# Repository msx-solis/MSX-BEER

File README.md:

# MSX-BEER
The MSX-Beer202 is a simple IDE interface for the MSX computers that not require to have more than 64K to use a hard disk. Original design by Solid and improved by some others (Yeti, FabF,...) in their own versions.

MSXmakers version 1.1 on "beer_ide_kicad" and "gerber" folders.

More info:

Links for ide-beer202:

Here you have very good instructions (in portuguesse). Talk about the problems with some 82c55 versions and how to format with "SD fortater".
(Full overWrite y size adjustament = on).

http://basshp.blogspot.com/2014/04/beer-202-ata-ide-review.html

Here you have a demostration video for this distribution: https://www.youtube.com/watch?v=AeNEiQcKNEI&t=1s

And here you have lots of BEER interface details

https://www.pjrc.com/tech/8051/ide/wesley.html

Some more links

https://www.msx.org/wiki/Beer_202

https://hansotten.file-hunter.com/do-it-yourself/beer-ide/

https://www.pjrc.com/tech/8051/ide/wesley.html

https://www.msx.org/es/news/software/es/beer-202-ide-interface-utilidad-de-particionado

https://www.msx.org/forum/msx-talk/hardware/beer-202-ide-interface?page=2

http://www.retrocomputacion.com/forum/hardware_msx/4440/experimentos-con-la-beer-interface-ide-para-msx-1-y-2/&p=2

Some files:

https://msx.org/forum/msx-talk/hardware/beer-ide-bios-19rc1-source-code-wanted?page=1

https://sysadminmosaic.ru/en/msx/beer_ide/beer_ide

Discussion about the version SD and some more files:

http://www.nedopc.org/forum/viewtopic.php?f=96&t=18820&sid=d75385e94fd1d6dbab35a1f73d379176&start=45#p144050

Another software to clone RAW disks called HDD Raw Copy Rool v1.10 (for windows):

http://www.hddguru.com/

Another system menu for game loading.

https://www.msxall.com/download/msxmenu-v1.68-beer.zip

And here you have a demostration video for this ditribution: https://www.youtube.com/watch?v=a2agPfgZmI0&t=596s

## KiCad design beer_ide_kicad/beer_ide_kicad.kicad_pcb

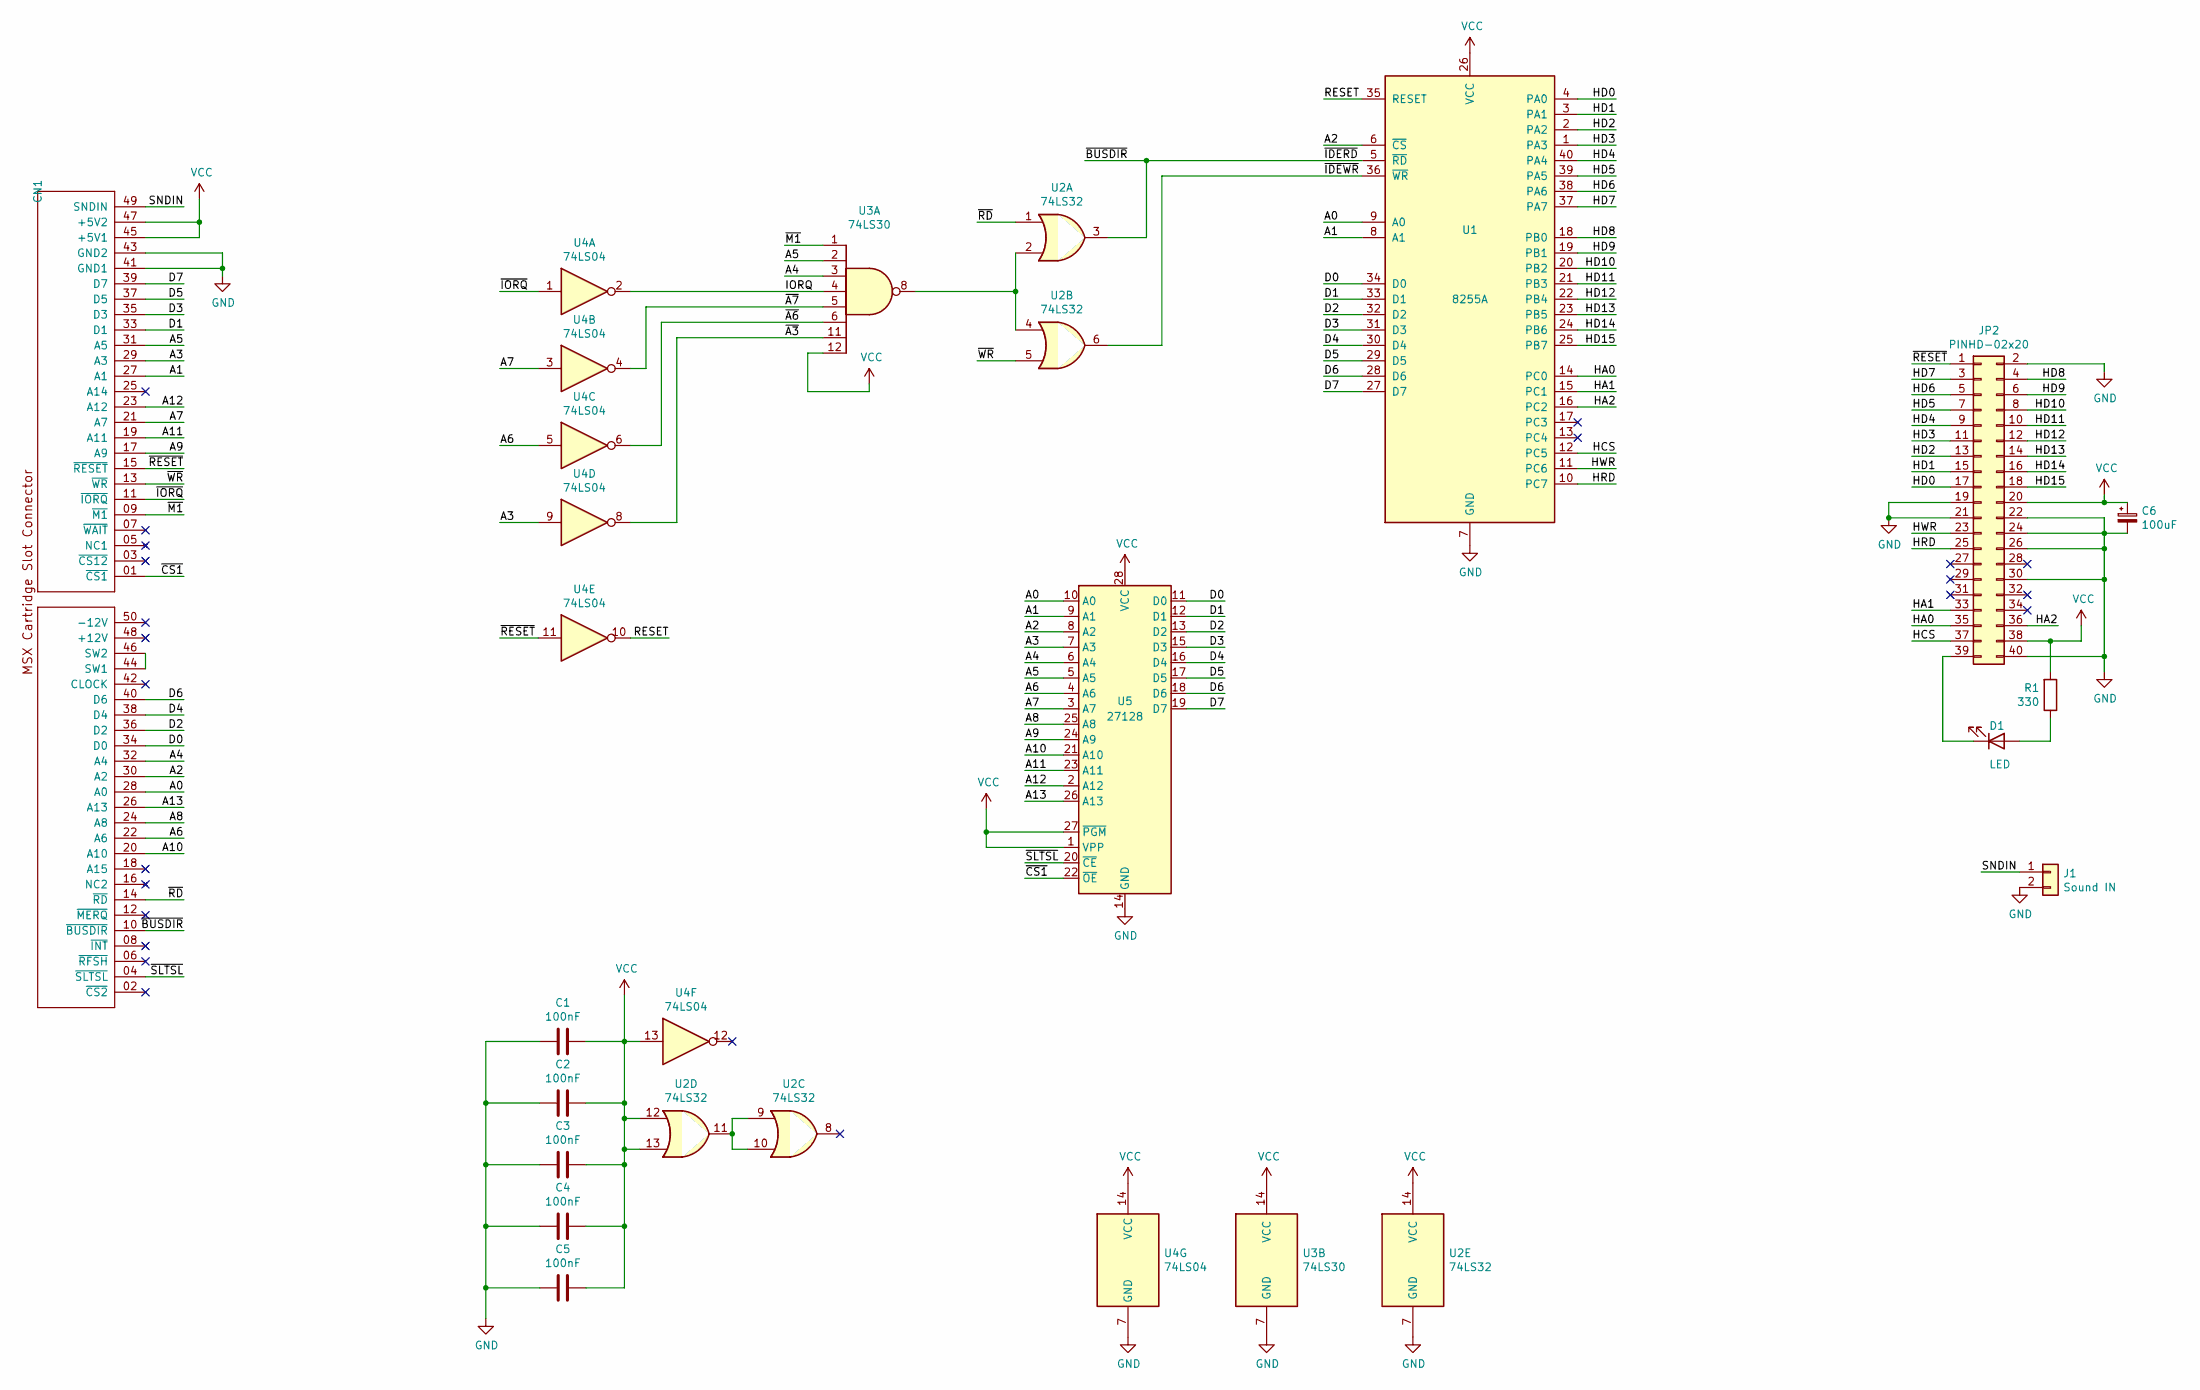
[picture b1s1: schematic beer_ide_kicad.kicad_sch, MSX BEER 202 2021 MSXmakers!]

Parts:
C1, C2, C3, C4, C5: 100nF; C_Disc_D4.7mm_W2.5mm_P5.00mm
C6: 100uF; CP_tumbado
CN1: MSX_SLOT_CON; CARTRIDGE_#_MSX_XL
D1: LED; LED_D3.0mm
J1: Sound IN; JST_EH_S2B-EH_1x02_P2.50mm_Horizontal
JP2: PINHD-02x20; PinHeader_2x20_P2.54mm_Horizontal
R1: 330; R_Axial_DIN0207_L6.3mm_D2.5mm_P7.62mm_Horizontal
U1: 8255A; DIP-40c_W15.24mm_LongPads
U2: 74LS32; DIP-14_W7.62mm_LongPads_0.9
U3: 74LS30; DIP-14c_W7.62mm_LongPads
U4: 74LS04; DIP-14c_W7.62mm_LongPads
U5: 27128; DIP-28c_W15.24mm_Socket_LongPads

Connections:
/A0: CN1.28 (A0), U1.9 (A0), U5.10 (A0)
/A1: CN1.27 (A1), U1.8 (A1), U5.9 (A1)
/A2: CN1.30 (A2), U1.6 (~CS), U5.8 (A2)
/A3: CN1.29 (A3), U4.9, U5.7 (A3)
/A4: CN1.32 (A4), U3.3, U5.6 (A4)
/A5: CN1.31 (A5), U3.2, U5.5 (A5)
/A6: CN1.22 (A6), U4.5, U5.4 (A6)
/A7: CN1.21 (A7), U4.3, U5.3 (A7)
/A8: CN1.24 (A8), U5.25 (A8)
/A9: CN1.17 (A9), U5.24 (A9)
/A10: CN1.20 (A10), U5.21 (A10)
/A11: CN1.19 (A11), U5.23 (A11)
/A12: CN1.23 (A12), U5.2 (A12)
/A13: CN1.26 (A13), U5.26 (A13)
/D0: CN1.34 (D0), U1.34 (D0), U5.11 (D0)
/D1: CN1.33 (D1), U1.33 (D1), U5.12 (D1)
/D2: CN1.36 (D2), U1.32 (D2), U5.13 (D2)
/D3: CN1.35 (D3), U1.31 (D3), U5.15 (D3)
/D4: CN1.38 (D4), U1.30 (D4), U5.16 (D4)
/D5: CN1.37 (D5), U1.29 (D5), U5.17 (D5)
/D6: CN1.40 (D6), U1.28 (D6), U5.18 (D6)
/D7: CN1.39 (D7), U1.27 (D7), U5.19 (D7)
/HA0: JP2.35, U1.14 (PC0)
/HA1: JP2.33, U1.15 (PC1)
/HA2: JP2.36, U1.16 (PC2)
/HCS: JP2.37, U1.12 (PC5)
/HD0: JP2.17, U1.4 (PA0)
/HD1: JP2.15, U1.3 (PA1)
/HD2: JP2.13, U1.2 (PA2)
/HD3: JP2.11, U1.1 (PA3)
/HD4: JP2.9, U1.40 (PA4)
/HD5: JP2.7, U1.39 (PA5)
/HD6: JP2.5, U1.38 (PA6)
/HD7: JP2.3, U1.37 (PA7)
/HD8: JP2.4, U1.18 (PB0)
/HD9: JP2.6, U1.19 (PB1)
/HD10: JP2.8, U1.20 (PB2)
/HD11: JP2.10, U1.21 (PB3)
/HD12: JP2.12, U1.22 (PB4)
/HD13: JP2.14, U1.23 (PB5)
/HD14: JP2.16, U1.24 (PB6)
/HD15: JP2.18, U1.25 (PB7)
/HRD: JP2.25, U1.10 (PC7)
/HWR: JP2.23, U1.11 (PC6)
/IORQ: U3.4, U4.2
/RESET: U1.35 (RESET), U4.10
/SNDIN: CN1.49 (SNDIN), J1.1
/~A3: U3.11, U4.8
/~A6: U3.6, U4.6
/~A7: U3.5, U4.4
/~BUSDIR: CN1.10 (~BUSDIR), U1.5 (~RD), U2.3
/~CS1: CN1.01 (~CS1), U5.22 (~OE)
/~IDEWR: U1.36 (~WR), U2.6
/~IORQ: CN1.11 (~IORQ), U4.1
/~M1: CN1.09 (~M1), U3.1
/~RD: CN1.14 (~RD), U2.1
/~RESET: CN1.15 (~RESET), JP2.1, U4.11
/~SLTSL: CN1.04 (~SLTSL), U5.20 (~CE)
/~WR: CN1.13 (~WR), U2.5
GND: C1.2, C2.2, C3.2, C4.2, C5.2, C6.2, CN1.41 (GND1), CN1.43 (GND2), J1.2, JP2.2, JP2.19, JP2.21, JP2.22, JP2.24, JP2.26, JP2.30, JP2.40, U1.7 (GND), U2.7 (GND), U3.7 (GND), U4.7 (GND), U5.14 (GND)
unnamed: CN1.44 (SW1), CN1.46 (SW2)
unnamed: D1.1 (K), JP2.39
unnamed: D1.2 (A), R1.1
unnamed: U2.2, U2.4, U3.8
unnamed: U2.9, U2.10, U2.11
VCC: C1.1, C2.1, C3.1, C4.1, C5.1, C6.1, CN1.45 (+5V1), CN1.47 (+5V2), JP2.20, JP2.38, R1.2, U1.26 (VCC), U2.12, U2.13, U2.14 (VCC), U3.12, U3.14 (VCC), U4.13, U4.14 (VCC), U5.1 (VPP), U5.27 (~PGM), U5.28 (VCC)

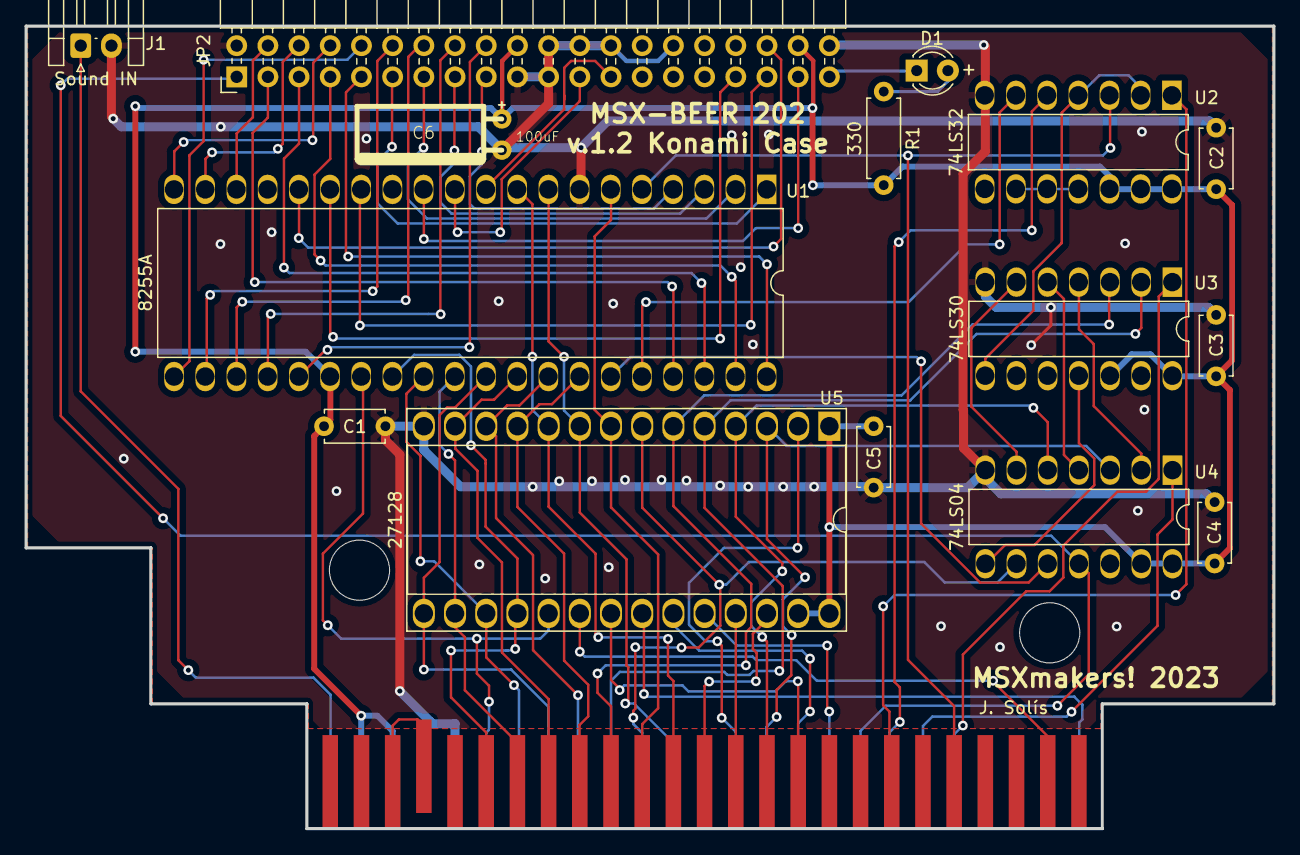
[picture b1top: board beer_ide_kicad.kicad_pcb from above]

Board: 2 copper layers, 101.6 x 65.3 mm, 16 parts (0 on the bottom side), 66 nets.

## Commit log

2023-03-16 adding video links
2023-10-27 new case design added
